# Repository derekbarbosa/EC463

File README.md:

<div align="center">

  <h1> :skull: VETCON BADGE :skull: </h1>
  
  <p>
    TEAM 32 <span> · </span>2021-2022  
  </p>
  <p>
  SEMPER DISCO
  </p>

<!-- Badges -->
<p>

</p>

<h3>
  Quick Links!
</h3>
<h4>
    <a href="PLACEHOLDER">View Demo</a>
  <span> · </span>
    <a href="notes/README_Engineering.md">Quick Start Guide</a>
  <span> · </span>
    <a href="notes/README_HARDWARE.md">Hardware Guide</a>
  <span> · </span>
    <a href="notes/README_SOFTWARE.md">Software Guide</a>
</h4>

</div>

<br />

<!-- Table of Contents -->
# :notebook_with_decorative_cover: Table of Contents

- [:notebook_with_decorative_cover: Table of Contents](#notebook_with_decorative_cover-table-of-contents)
  - [:star2: About the Project](#star2-about-the-project)
    - [:label: Current Directory Structure](#label-current-directory-structure)
    - [:camera: Screenshots](#camera-screenshots)
    - [:space_invader: Tech Stack](#space_invader-tech-stack)
    - [:dart: Features](#dart-features)
      - [Embedded](#embedded)
      - [Minigames](#minigames)
  - [:toolbox: Getting Started](#toolbox-getting-started)
    - [:running: Quick(ly) Start!](#running-quickly-start)
  - [:eyes: Usage](#eyes-usage)
  - [:warning: License](#warning-license)
  - [:handshake: Contact](#handshake-contact)
  - [:gem: Acknowledgements](#gem-acknowledgements)

<!-- About the Project -->
## :star2: About the Project

### :label: Current Directory Structure
<a href="pcb/">pcb</a> – All PCB/eCAD files and schematics. Includes manufacturing .gbr files

<a href="platformio/">platformio</a> – All code/firmware files concerning the MSP430 development board

<a href="notes/">notes</a> – Inital interview notes, MSP Documentation, useful infographics, additional READMEs

<a href="minigames/">minigames</a> – All code regarding Games 1, 2, and 3 (with CMake Files)

<a href="reports/">reports</a> – All previous reports for the 2021-2022 semester

<a href="derek/">derek</a> – Derek's personal folder for logbook maintenance

<a href="kircher/">kircher</a> – John's personal folder for logbook maintenance

<a href="etc/">etc</a> – Asset storage (logos, etc.)

<!-- Screenshots -->
### :camera: Screenshots

<div align="center"> 
  <p> PlatformIO VSCode Plugin "Home" Page </p>
  
</div>

<div align="center"> 
  <p> Sample Terminal Menu via Serial </p>
  
</div>

<div align="center"> 
  <p> Minigame #1 "Dino Run"</p>
  
</div>

<div align="center"> 
  <p> Minigame #2 "Coin Flip" </p>
  
</div>
<div align="center"> 
  <p> Minigame #3 "Text-based adventure" </p>
  
</div>

<!-- TechStack -->
### :space_invader: Tech Stack

<details>
  <summary>Embedded</summary>
  <ul>
    <li><a href="https://www.cplusplus.com/">C++</a></li>
    <li><a href="https://piolabs.com/company/about.html">PIOLabs</a></li>
    <li><a href="PlatformIO">PlatformIO</a></li>
    <li><a href="https://sourceforge.net/projects/mspgcc/">GCC Toolchain for MSP430 by TI</a></li>
    <li><a href="https://energia.nu/reference/">Energia Wiring-based Framework</a></li>
    <li><a href="https://registry.platformio.org/tools/platformio/tool-dslite">Uniflash Flash Tool for TI MCUs</a></li>
    <li><a href="http://wiring.org.co/">Wiring MCU Framework</a></li>
  </ul>
</details>

<details>
  <summary>Minigames</summary>
  <ul>
    <li><a href="https://phaser.io/">Phaser</a></li>
    <li><a href="https://webpack.js.org/">Webpack</a></li>
    <li><a href="https://www.typescriptlang.org/">Typescript</a></li>
    <li><a href="https://enable3d.io/">Enable3D</a></li>
    <li><a href="https://www.javascript.com/">Javascript</a></li>
    <li><a href="https://developer.mozilla.org/en-US/docs/Glossary/HTML5">HTML5</a></li>    
    <li><a href="https://cmake.org/">CMake</a></li>
  </ul>
</details>

<!-- Features -->
### :dart: Features

#### Embedded
- Interactive Shell/Terminal "UI"
- Customizeable
- Built-in LED Toggles
- Bluetooth Capable!
- Built-in low-power directives

#### Minigames
<details>
<summary> Game 1 </summary>
<ul>
<li> Interactive 'runner' game </li>
<li> Obfustication of source using Webpack and Babel for compilation</li>
<li> Hidden 'secrets' ;) </li>
</ul>
</details>
<details>
<summary> Game 2 </summary>
<ul>
<li> Interactive UI elements</li>
<li> Fluid animation using CSS! </li>
<li> Lightweight in-line JS </li>
<li> Built-in cookie storage and retrieval</li>
<li> Hidden 'secrets' ;) </li>
</ul>
</details>
<details>
<summary> Game 3</summary>
<ul>
<li> Interactive decision-based RPG-like text adventure </li>
<li> Open-ended Game Engine with Global Update features for future development and hackability </li>
<li> Text Engine incorporated at Compile-Time with simple .tsv formatting </li>
<li> Built-in undetectable "malware" with std::Threads </li>
<li> Hidden 'secrets' ;) </li>
</ul>
</details>

<!-- Getting Started -->
## 	:toolbox: Getting Started

<!-- Run Locally -->
### :running: Quick(ly) Start!

Clone the project

```bash
  git clone https://github.com/derekbarbosa/EC463.git
```

Then refer to the Quick Start Guide in its entirety! :)
[Quick Start Guide](notes/README_Engineering.md)

<!-- Usage -->
## :eyes: Usage

For a more detailed breakdown of the software components, how they work, how to implement them and how to expand on them, please refer to the [Software Guide](./notes/README_SOFTWARE.md)

For notes and explanation regarding hardware, building a functional breadboard prototype, understanding the modularity of several components, and PCB breakdown, please refer to the [Hardware Guide](./notes/README_HARDWARE.md)

<!-- License -->
## :warning: License

Distributed under the GNU GPL v3 LICENSE. See  <a href="https://www.github.com/derekbarbosa/EC463/blob/main/LICENSE">LICENSE.TXT</a> for more information.

<!-- Contact -->
## :handshake: Contact

<h4>Client</h4>

Mike Jones - jonesmlr (AT) gmail (dot) com

<h4> Team Members </h4>

<br> Derek Barbosa - dbarbosa (AT) bu (dot) edu </br>
<br> Ryan Sullivan - ryanbs (AT) bu (dot) edu </br>
<br> John Kircher - kircherj (AT) bu (dot) edu </br>
<br> Julian Padgett - jpadgett (AT) bu (dot) edu </br>
<br> Carlos Ortiz - cartex10 (AT) bu (dot) edu </br>

<br> Project Link: [https://github.com/derekbarbosa/EC463](https://github.com/derekbarbosa/EC463) </br>

<!-- Acknowledgments -->
## :gem: Acknowledgements

Some shout-outs, acknowledgements and resources!

 - [Shields.io](https://shields.io/)
 - [Awesome README](https://github.com/matiassingers/awesome-readme)
 - [Emoji Cheat Sheet](https://github.com/ikatyang/emoji-cheat-sheet/blob/master/README.md#travel--places)
 - [Make your own Dino Chrome Game!](https://www.youtube.com/watch?v=VOtZ6yNqH84)
 - [Using a 16x2 LCD with Arduino](https://www.makerguides.com/character-lcd-arduino-tutorial/)
 - [Making a Coin Toss Game](https://www.foolishdeveloper.com/2021/10/coin-flip-game-using-javascript.html)

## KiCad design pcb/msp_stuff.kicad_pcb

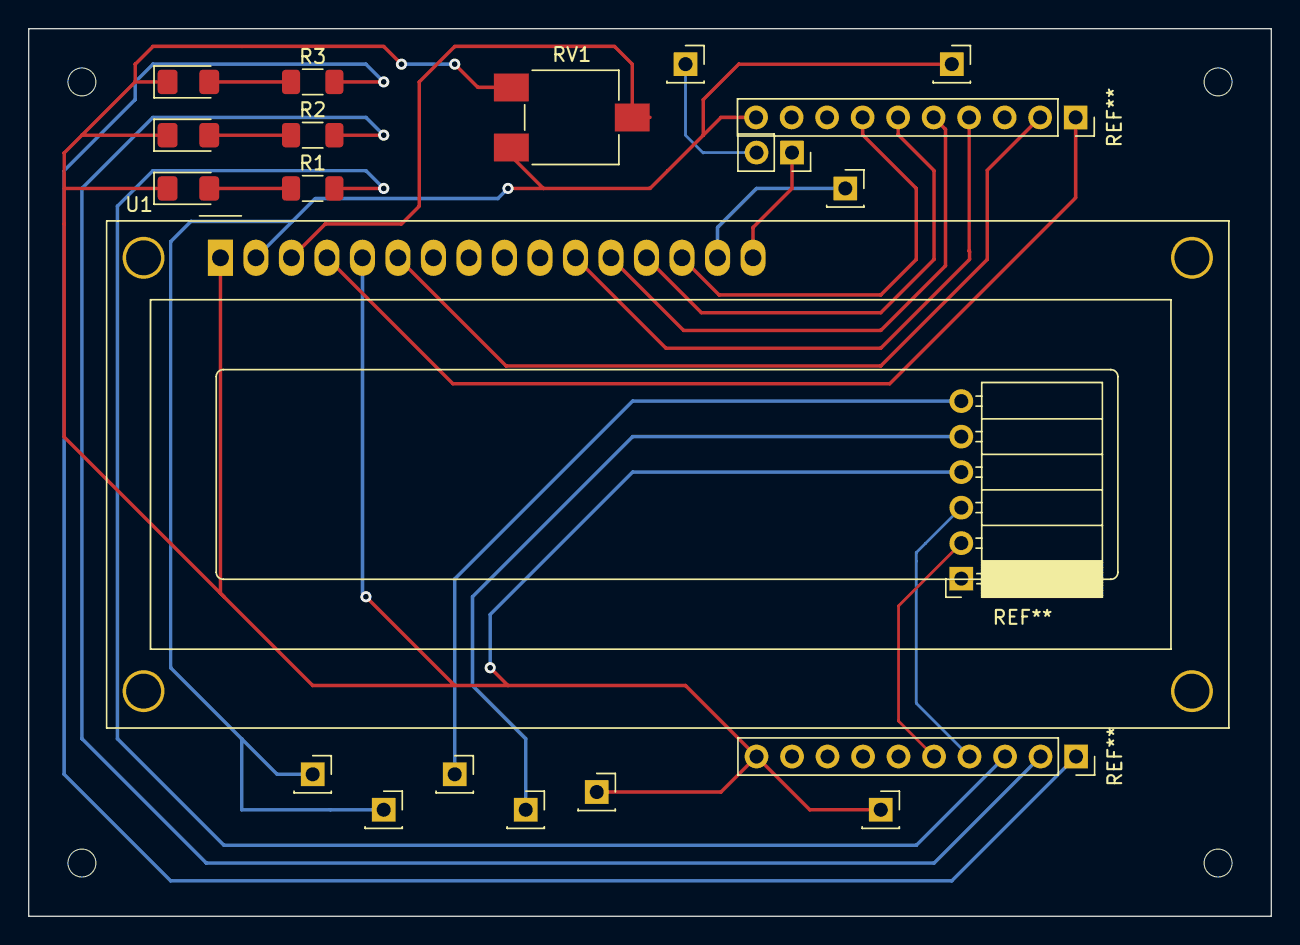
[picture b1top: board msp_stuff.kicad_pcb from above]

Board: 2 copper layers, 88.9 x 63.5 mm, 8 parts (0 on the bottom side), 6 nets.

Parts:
D1, D2, D3: LED; LED_1206_3216Metric_Pad1.42x1.75mm_HandSolder
R1, R2, R3: R_Small_US; R_1206_3216Metric_Pad1.30x1.75mm_HandSolder
RV1: R_Potentiometer; Potentiometer_ACP_CA6-VSMD_Vertical
U1: RC1602A-GHW-ESX; WC1602A

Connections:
+BATT: RV1.1, U1.2 (VDD), U1.15 (A/VEE)
GND: D1.1 (K), D2.1 (K), D3.1 (K), RV1.3, U1.1 (VSS), U1.5 (R/~W), U1.16 (K)
unnamed: D1.2 (A), R1.1
unnamed: D2.2 (A), R2.1
unnamed: D3.2 (A), R3.1
unnamed: RV1.2, U1.3 (Vo)

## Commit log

2021-09-23 first commit to repo
2021-09-23 updated readme and logbook 9/22
2021-09-23 updating with other files
2021-09-24 adding initial description questions
2021-09-24 updating repo structure
2021-09-24 Finished adding questions
2021-09-24 pushing cleanup
2021-09-24 add questions for 9-24 interview
2021-09-24 added logbook push
2021-09-24 update readme with my contact info
2021-09-24 updating doc last minute
2021-09-24 added notes from the interview session
2021-09-27 updated derek logbook
2021-09-28 LogBook for Kircher created
2021-09-29 derek logbook update 9-28
2021-10-01 updated logbook
2021-10-07 logbook update 10/6/21
2021-10-12 forgot to push over the weekend, added oct 12th entry
2021-10-14 10/14/21 commit
2021-10-18 update 10/18/21
2021-10-21 last commit before logbook review
2021-10-26 Created, debugged, built and flashed a MSP430FR2433 hello world program that blinks an LED
2021-10-27 Create LICENSE
2021-11-02 adding bootloader to src
2021-11-02 adding mspboot and apps to repo
2021-11-02 cleaned up stuff. Deleted old objects and cloned samples of bootloader into repo
2021-11-03 attempting to figure out what is going on with gmake compile errors
2021-11-03 logbook
2021-11-04 logbook edit
2021-11-04 adding src
2021-11-04 new bootloader project
2021-11-04 removing trash
2021-11-04 fix target configuration
2021-11-09 update logbook
2021-11-10 logbook update
2021-11-11 initialize menu control structure
2021-11-12 adding platformio files
2021-11-13 prototype progress
2021-11-14 almost done with prototyping
2021-11-14 Update main.cpp
    Added Reset Option, included a secret, utilized buttons for secret menu. Added option 4 and 9 to menu.
2021-11-15 got button pushes working
2021-11-15 Updated main.cpp, ready for merge to testing
2021-11-16 cleaning up .swp
2021-11-16 added button functionality
2021-11-16 add dino game into webgame folder
2021-11-16 Prototype Code, Ready For Testing
2021-11-18 last logbook push
2021-12-03 push after a long time
2022-01-26 Updating logbook with push, forgot to push over the break
2022-01-31 logbook push
2022-02-03 adding game 3
2022-02-08 implemented persistent memory of flags TODO: store name persistently
2022-02-10 repo cleanup
2022-02-10 pushing some repo changes
2022-02-10 added in persistent string variables
2022-02-15 finished welcome sequence
2022-02-17 moving onto scenario 1
2022-02-17 testing crash functionality
2022-02-18 pushing scenarios.h
2022-02-22 Updated flags for games 1 & 2, added led functionality
2022-02-24 pushing changes to struct
2022-02-24 created file parser, edited scope of function. Need to implement main game loop and debug
2022-02-24 forgot to push the .tsv file
2022-02-24 fixed dup symbol erro
2022-02-25 broken right now, segfault on line 23
2022-02-25 pushing up for ryan to debug mem allocation
2022-02-25 adding logbook push
2022-02-25 forgot to add this->refs to class
2022-02-28 new in main vs new in functions file yields diff results
2022-03-01 getting issues with dereferncing game scenario struct
2022-03-01 fixed pointer passing for constructScenarioList
2022-03-01 led checks updated
2022-03-01 made sure all fields are properly assigned
2022-03-01 finished inline string parser and struct allocation
2022-03-01 fixed string parsing for consequence points
2022-03-01 edited .tsv
2022-03-01 added in point parsing in main game loop
2022-03-01 prototype is ready 2 go
2022-03-01 Updated new BLE
2022-03-02 pushing up finished game 3
2022-03-02 fixed minor bugs
2022-03-03 forgot to push new .tsv
2022-03-03 updated ble functions and menus
2022-03-03 pushing logbook before merge
2022-03-03 removing webgames folder, webgames is located on derekbarbosa/EC463WebGames
2022-03-03 removing CCStudio SRC library
2022-03-17 Bluetooth UpdatedWorkingConnection
2022-03-17 forgot to push up my changes to prevent segfaulting on argv
2022-03-21 Bluetooth Working, Secrets All Updated
2022-03-22 cleanup to start share session
2022-03-22 Updated Pins
2022-03-22 Pins Out Finalized, Working software :)
2022-03-22 updated ble delay
2022-03-23 Code refactor/cleanup for readability. Added quit option using prompt on BT module
2022-03-28 updating logbooks
2022-03-29 editing makefile to compile a static macOS binary, first attempt
2022-03-29 editing make rules
2022-03-29 adding additional cflush
2022-03-29 linux compatible (hopefully)
2022-03-30 WIP not GUARANTEED TO WORK
2022-03-31 forgot to push changes last night, interrupt progress + logbook update
2022-03-31 having trouble with LED Menu controls and interrupt with push buttons
2022-03-31 Bluetooth Switches Working
2022-04-01 logbok + attempt to fix push2
2022-04-04 refactors, LED menu complete, sleep mode in operation succesfully
2022-04-05 slight refactor to .cpp, logbook push
2022-04-07 pushing last logbook change
2022-04-14 cmake cross compilation
2022-04-14 pushing edited cmake file
2022-04-15 beginning of git restructuring
2022-04-15 restructuring folders, moving text_based game to root dir
2022-04-15 renaming 'Test' to 'VETCON'
2022-04-15 adding pcb files to github
2022-04-15 adding structure to notes, placeholder for needed files
2022-04-19 init SOFTWARE README report
2022-04-19 add in reports compiled
2022-04-20 github mgmt and readme changes
2022-04-20 continued restructuring of repo, commencing the 'pruning' of old branches
2022-04-20 updated repo README.md with template
2022-04-20 readme edits
2022-04-20 pushing changes
2022-04-20 attempting to add node_modules to gitignore
2022-04-20 deleted node_modules/
2022-04-20 finished repo README.md and README_Engineering.md
2022-04-20 quick edits to filepaths
2022-04-21 update bluetooth buttons
2022-04-21 adding a pcb enclosure folder to track .stl files
2022-04-21 pushing readme changes to reflect repo changes
2022-04-21 fix screen and bluetooth
2022-04-21 updated fab files for jlcpcb
2022-04-26 updated README_SOFTWARE.md format
2022-04-27 added in some context to the MCU code
2022-04-27 Add template for hw report
2022-04-28 add images for hw report
2022-04-28 add hw report images
2022-04-28 updated README_SOFTWARE.md
2022-04-28 added power supply constraints :)
2022-04-28 adding SW report changes
2022-04-28 bluetooth done
2022-04-28 finished SW report and edited parts of HW report
2022-04-29 adding PCB purchase instructions
2022-04-29 add jpgs for hw report
2022-04-29 edit HW report images
2022-04-29 adding final STL enclosure, finishing touches on HW report
2022-05-01 including one more item in BOM
2022-05-06 final STL case
